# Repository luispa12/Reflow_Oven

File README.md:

# Open Source Reflow Oven

## Introduction
The reflow Oven is a custom made PCB, based on the design from RocketScream (tiny reflow oven), it is based on the atmega328p, featuring a MAX31865 to control the thermocuple, an Oled LCD to see the reflow process on real time.

## Project Description
Detailed description of the hardware project, including its purpose, objectives, and unique features.

This project was done with the idea of having my own reflow oven at home, so I can do the manufacturing process at my lab, it consist on only 3 main components, the PCB, an SSR and, of course, a oven.

## Design Process
Insights into the design process, challenges faced, and key design decisions made.

For this project, I wanted the PCB to be the smallest I can, but taking into consideration that I don't have proper tools to assemble it at home (the reason why I'm doing this reflow oven), so I decided to use 0806 components, which can be relativily easy to solder by hand and a heat gun.
The most difficult component to solder was the Atmega328 because I only got the QFN package, which is very small, but after a lot of attempts I was able to solder it succesfully.

I also needed the pcb to be small enough to fit inside the oven without doing so much modification, and have a small overall footprint.

Documentation is still on progress...

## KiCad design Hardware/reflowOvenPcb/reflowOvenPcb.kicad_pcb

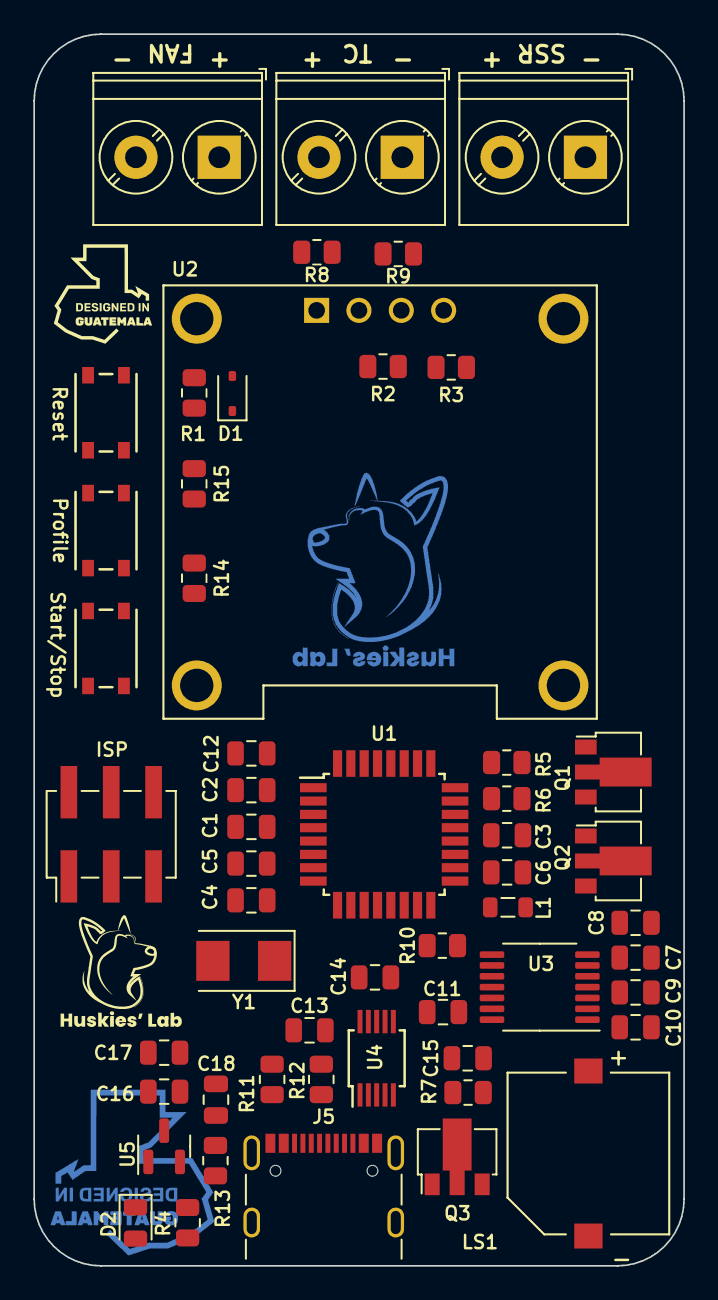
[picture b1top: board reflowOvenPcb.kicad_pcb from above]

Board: 2 copper layers, 39.0 x 73.9 mm, 54 parts (0 on the bottom side), 41 nets.

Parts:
C1, C2, C3, C6, C8, C10, C11, C13, C14, C15, C16: 100nF; C_0805_2012Metric
C4, C5: 10pF; C_0805_2012Metric
C7, C9, C12: 10nF; C_0805_2012Metric
C17, C18: 10 uF 16V; C_0805_2012Metric
D1: 1N4148WS; D_SOD-323
D2: LED; LED_0805_2012Metric
Fan: Fan_output; TerminalBlock_Phoenix_PT-1,5-2-5.0-H_1x02_P5.00mm_Horizontal
ISP: ISP; PinHeader_2x03_P2.54mm_Vertical_SMD
J5: USB_C_Receptacle_USB2.0; USB_C_Receptacle_GCT_USB4105-xx-A_16P_TopMnt_Horizontal
L1: L; L_0805_2012Metric
LS1: Buzzer; CUI_CMI-9705-0580-SMT-TR
Profile: Perfil; SW4_PTS815 SJM 250 SMTR LFS_CNK
Q1, Q2, Q3: 2N3904; SOT-89-3
R1, R10: 10K; R_0805_2012Metric
R2, R3, R4, R14, R15: 2.2K; R_0805_2012Metric
R5, R6: 53K5; R_0805_2012Metric
R7: 27K; R_0805_2012Metric
R8, R9: 100R; R_0805_2012Metric
R11, R12: 5.11K; R_0805_2012Metric
R13: 1M; R_0805_2012Metric
Reset: RST_Button; SW4_PTS815 SJM 250 SMTR LFS_CNK
SRR: SSR_Output; TerminalBlock_Phoenix_PT-1,5-2-5.0-H_1x02_P5.00mm_Horizontal
Start/Stop: Start/Stop; SW4_PTS815 SJM 250 SMTR LFS_CNK
TC: Thermocouple; TerminalBlock_Phoenix_PT-1,5-2-5.0-H_1x02_P5.00mm_Horizontal
U1: ATmega328-M; TQFP-32_7x7mm_P0.8mm
U2: DM-OLED096-636; MODULE_DM-OLED096-636
U3: MAX31856; TSSOP-14_4.4x5mm_P0.65mm
U4: CH340E; MSOP-10_3x3mm_P0.5mm
U5: MCP1700x-330xxTT; SOT-23
Y1: 8Mhz; Crystal_SMD_5032-2Pin_5.0x3.2mm

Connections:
+3.3V: C1.2, C2.1, C10.2, C11.2, C12.2, C14.2, C18.2, D1.1 (K), ISP.4, L1.1, R1.2, R2.2, R3.2, R10.2, R14.2, R15.2, U2.2 (VCC_IN), U3.5 (AVDD), U3.8 (DVDD), U4.7 (VCC), U5.2 (VO)
+5V: C16.1, C17.2, Fan.1, J5.A4 (VBUS), J5.A9 (VBUS), J5.B4 (VBUS), J5.B9 (VBUS), LS1.P, SRR.1, U5.3 (VI)
/A0: R6.1, U1.23 (PC0)
/A1: R5.1, U1.24 (PC1)
/D0: U1.30 (PD0), U4.8 (TXD)
/D1: U1.31 (PD1), U4.9 (RXD)
/D2: Profile.4, R15.1, U1.32 (PD2)
/D3: R14.1, Start/Stop.4, U1.1 (PD3)
/D4: R4.2, U1.2 (PD4)
/D5: R7.1, U1.9 (PD5)
/D9: U1.13 (PB1), U3.13 (~FAULT)
/D10: R10.1, U1.14 (PB2), U3.9 (~CS)
/D11: ISP.5, U1.15 (PB3), U3.10 (SCK)
/D12: ISP.1, U1.16 (PB4), U3.11 (SDO)
/D13: ISP.2, U1.17 (PB5), U3.12 (SDI)
/D+: J5.A6 (D+), J5.B6 (D+), U4.1 (UD+)
/D-: J5.A7 (D-), J5.B7 (D-), U4.2 (UD-)
/RST: C15.1, D1.2 (A), ISP.3, R1.1, Reset.4, U1.29 (~RESET/PC6)
/SCL: R2.1, U1.28 (PC5), U2.3 (SCL)
/SDA: R3.1, U1.27 (PC4), U2.4 (SDA)
/TC+: R8.1, TC.2
/TC-: R9.1, TC.1, U3.2 (BIAS)
/XTAL1: C5.1, U1.7 (XTAL1/PB6), Y1.1
/XTAL2: C4.1, U1.8 (XTAL2/PB7), Y1.2
GND: C1.1, C2.2, C3.1, C4.2, C5.2, C6.1, C7.1, C9.2, C10.1, C11.1, C12.1, C13.1, C14.1, C16.2, C17.1, C18.1, D2.1 (K), ISP.6, J5.A1 (GND), J5.A12 (GND), J5.B1 (GND), J5.B12 (GND), Profile.1, Q1.1 (E), Q2.1 (E), Q3.1 (E), R11.2, R12.2, R13.1, Reset.1, Start/Stop.1, U1.3 (GND), U1.4 (VCC), U1.5 (GND), U1.6 (VCC), U1.21 (GND), U2.1 (GND), U3.1 (AGND), U3.14 (DGND), U4.3 (GND), U5.1 (GND)
unnamed: D2.2 (A), R4.1
unnamed: Fan.2, Q1.3 (C)
unnamed: Q2.3 (C), SRR.2
unnamed: J5.A5 (CC1), R11.1
unnamed: J5.B5 (CC2), R12.1
unnamed: J5.S1 (SHIELD), R13.2
unnamed: Q1.2 (B), R5.2
unnamed: Q2.2 (B), R6.2
unnamed: Q3.2 (B), R7.2
unnamed: LS1.N, Q3.3 (C)
unnamed: C3.2, U1.20 (AREF)
unnamed: C6.2, L1.2, U1.18 (AVCC)
unnamed: C7.2, C8.1, R8.2, U3.4 (T+)
unnamed: C8.2, C9.1, R9.2, U3.3 (T-)
unnamed: C13.2, U4.10 (V3)
unnamed: C15.2, U4.4 (~RTS)

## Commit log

2024-01-10 added gitignore file
2024-01-10 added the folders for rest of the gfiles
2024-01-10 added rest of files
2024-01-10 gitignore
2024-04-30 initial
2024-04-30 modified the gitignore
2024-05-01 created kicad project
2024-05-01 gitignore modification
2024-05-01 added photo file
2024-05-01 Remove .DS_Store from everywhere
2024-05-01 PCB: started to add components
2024-05-01 readme.md
2024-05-01 read .md
2024-05-02 MCU wiring finished, added components to OLED SSD
2024-05-02 Added the 3d file and libvraries for oled SSD creen
2024-05-02 added the readme.
2024-05-03 PCB EE: added ssr, fan and buzzer modulo
2024-05-17 Added multiple libraris, and place all the components
2024-05-18 modified the layout of the board, and made some placement of the components
2024-05-18 modified the readme description
